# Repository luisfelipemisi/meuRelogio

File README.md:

# meuRelogio
Construção de um relógio utilizando um arduino uno, 4 displays de 8 segmentos, um rtc e dois botões.

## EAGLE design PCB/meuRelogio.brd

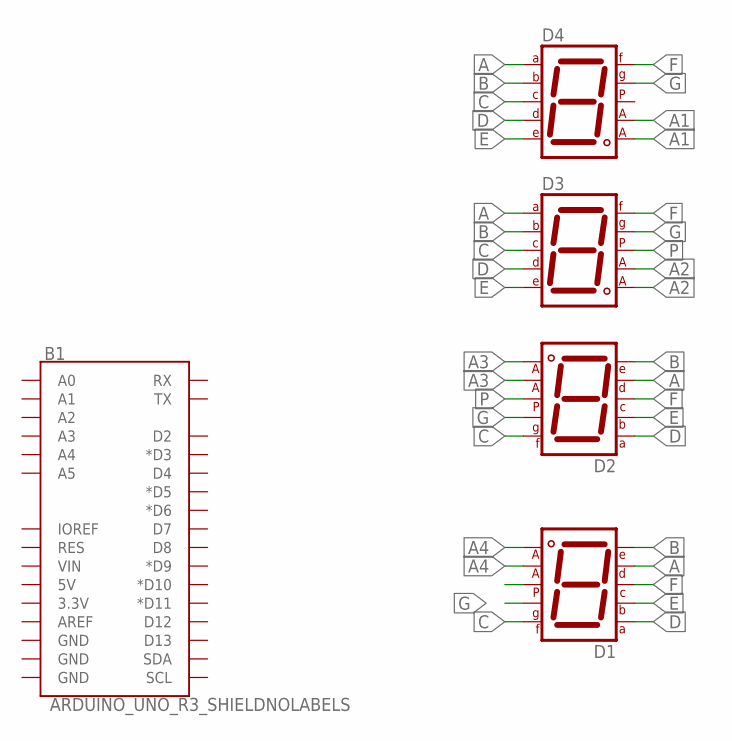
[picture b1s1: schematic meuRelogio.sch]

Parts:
B1: ARDUINO_UNO_R3_SHIELDNOLABELS; UNO_R3_SHIELD_NOLABELS
D1, D2, D3, D4: 7SEG-CA; 7SEG-13

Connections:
A: D1.2 (D), D2.2 (D), D3.7 (A), D4.7 (A)
A1: D4.3 (CA1), D4.8 (CA2)
A2: D3.3 (CA1), D3.8 (CA2)
A3: D2.3 (CA1), D2.8 (CA2)
A4: D1.3 (CA1), D1.8 (CA2)
B: D1.1 (E), D2.1 (E), D3.6 (B), D4.6 (B)
C: D1.9 (F), D2.9 (F), D3.4 (C), D4.4 (C)
D: D1.7 (A), D2.7 (A), D3.2 (D), D4.2 (D)
E: D1.6 (B), D2.6 (B), D3.1 (E), D4.1 (E)
F: D1.4 (C), D2.4 (C), D3.9 (F), D4.9 (F)
G: D1.10 (G), D2.10 (G), D3.10 (G), D4.10 (G)
P: D2.5 (DP), D3.5 (DP)

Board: 2 copper layers, 5 parts (0 on the bottom side), 12 nets, no tracks yet.

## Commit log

2021-10-10 horário funcional, edição de data e hora funcional
2021-10-10 update nome
2021-10-10 Adicionando arquivo README
2021-10-10 update readme2
2021-10-10 update readme3
2021-10-10 alarme adicionado com melodia
2021-10-10 variáveis da função config mode vais legíveis
2021-10-10 pontos piscam com mudança dos segundos; bug do dia da semana corrigido;
2021-10-10 correção de botões para edição do alarme
2021-10-12 pomodoro adicionado; interface de seleção adicionada; correção de bug dos botões; correção do bug do day of week
2021-10-12 add songs
2021-10-12 alarme com opções de musicas
2021-10-12 pomodoro com música; pause pomodoro
2021-10-12 correção de bug da musica do pomodoro; correção de bug da volta do pause no pomodoro
2021-10-12 correção nos estados do pomodoro
2021-10-16 add projeto pcb
2021-10-16 add song 0; add time to back in pomodoro and config
2021-10-16 correção bug timetoback
2021-10-16 correção do bug do time do pomodoro
2021-10-16 add constante TIMETOBACK
2021-10-16 corrigido erro do LONGBREAK

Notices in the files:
parts and their libraries:
SparkFun-Boards: Licensing: Creative Commons ShareAlike 4.0 International - https://creativecommons.org/licenses/by-sa/4.0
